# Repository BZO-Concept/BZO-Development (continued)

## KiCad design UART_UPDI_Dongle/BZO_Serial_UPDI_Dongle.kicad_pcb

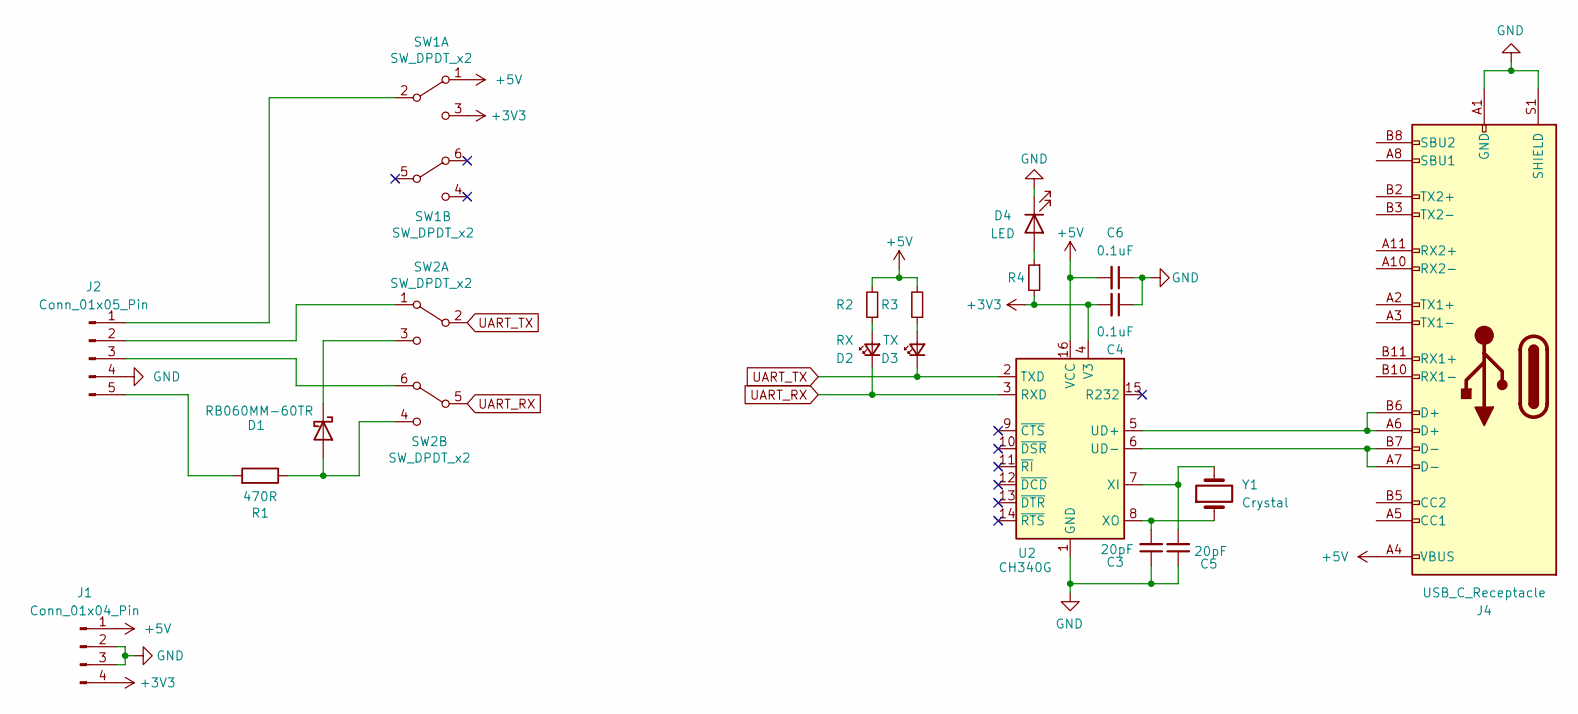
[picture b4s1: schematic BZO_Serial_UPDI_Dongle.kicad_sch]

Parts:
C3, C5: 20pF; C_0805_2012Metric_Pad1.18x1.45mm_HandSolder; LCSC Part # C0805C200J5HACTU
C4, C6: 0.1uF; C_0805_2012Metric_Pad1.18x1.45mm_HandSolder; LCSC Part # C0805C104J5RACTU
D1: RB060MM-60TR; LED_1206_3216Metric_Pad1.42x1.75mm_HandSolder(clean); Mouser Part Number 755-RB060MM-60TR
D2: RX; LED_1206_3216Metric_Pad1.42x1.75mm_HandSolder(clean); LCSC Part # //////////////////////////
D3: TX; LED_1206_3216Metric_Pad1.42x1.75mm_HandSolder(clean); LCSC Part # //////////////////////////
D4: LED; LED_1206_3216Metric_Pad1.42x1.75mm_HandSolder(clean); LCSC Part # //////////////////////////
J1: Conn_01x04_Pin; PinHeader_1x04_P2.54mm_Vertical; LCSC Part # //////////////////////////
J2: Conn_01x05_Pin; PinHeader_1x05_P2.54mm_Vertical; LCSC Part # //////////////////////////
J4: USB_C_Receptacle; USB_C_Receptacle_GCT_USB4085; LCSC Part # USB4085-GF-A
R1, R2, R3, R4: 470R; R_0805_2012Metric_Pad1.20x1.40mm_HandSolder; LCSC Part # CR0805-FX-4700ELF
SW1, SW2: SW_DPDT_x2; SMDIP-6_W7.62mm; LCSC Part # //////////////////////////
U2: CH340G; SOIC-16_3.9x9.9mm_P1.27mm; MANUFACTURER PART NUMBER CH340; LCSC Part # CH340G
Y1: Crystal; Crystal_SMD_HC49-SD

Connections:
+3V3: C4.2, J1.4, R4.2, SW1.3 (C), U2.4 (V3)
+5V: C6.2, J1.1, J4.A4 (VBUS), J4.A9 (VBUS), J4.B4 (VBUS), J4.B9 (VBUS), R2.2, R3.2, SW1.1 (A), U2.16 (VCC)
GND: C3.1, C4.1, C5.1, C6.1, D4.1 (K), J1.2, J1.3, J2.4, J4.A1 (GND), J4.A12 (GND), J4.B1 (GND), J4.B12 (GND), J4.S1 (SHIELD), U2.1 (GND)
unnamed: D1.2 (A), R1.1, SW2.4 (C)
unnamed: D1.1 (K), SW2.3 (C)
unnamed: D2.2 (A), R2.1
unnamed: D3.2 (A), R3.1
unnamed: D4.2 (A), R4.1
unnamed: J2.1, SW1.2 (B)
unnamed: J2.2, SW2.1 (A)
unnamed: J2.3, SW2.6 (A)
unnamed: J2.5, R1.2
unnamed: J4.A6 (D+), J4.B6 (D+), U2.5 (UD+)
unnamed: J4.A7 (D-), J4.B7 (D-), U2.6 (UD-)
unnamed: C5.2, U2.7 (XI), Y1.2
unnamed: C3.2, U2.8 (XO), Y1.1
UART_RX: D2.1 (K), SW2.5 (B), U2.3 (RXD)
UART_TX: D3.1 (K), SW2.2 (B), U2.2 (TXD)

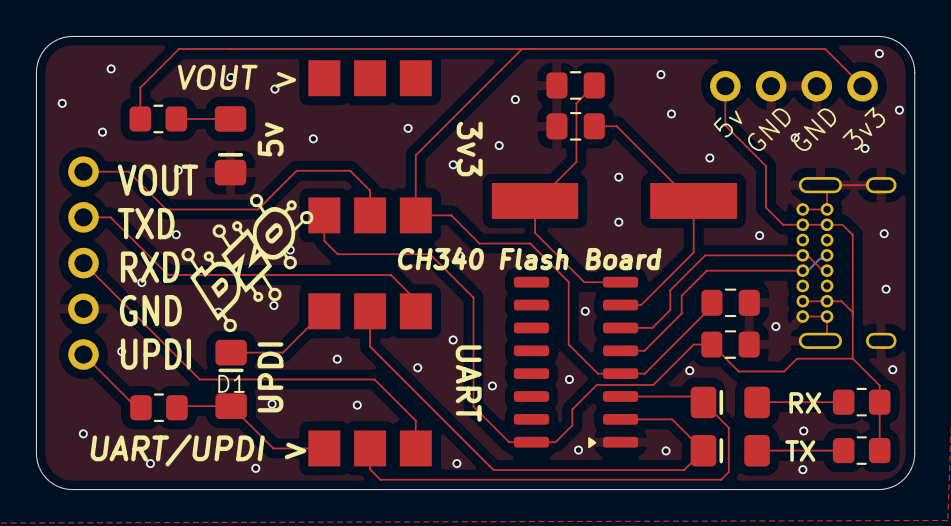
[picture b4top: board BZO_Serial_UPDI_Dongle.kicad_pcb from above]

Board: 2 copper layers, 48.8 x 25.2 mm, 19 parts (0 on the bottom side), 18 nets.

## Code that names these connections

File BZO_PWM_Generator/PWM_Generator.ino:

#include "BZO_PWM_Generator.h"

#define PinOUT1 PB0
#define PinOUT2 PB1
#define PinOUT3 PB10
#define PinOUT4 PB11

#define PinPOTvalue PA0
#define Frequence   150      //Hz
#define Duty        10       //%
#define WorkingValueMIN 50   //seuil min de traitement de la valeur
#define WorkingValueMAX 900  //seuil max de traitement de la valeur
#define DutyMIN   10         //valeur de Duty au seuil min %
#define DutyMAX   90         //valeur de Duty au seuil max %

uint16_t PotValue = 0;

void setup() {

  pinMode(PinPOTvalue, INPUT_ANALOG);
  //( Channel, Pin, Frequence, Duty, Valeur MIN, Valeur MAX, Duty/Freq MIN, Duty/Freq MAX)
  init_PWMG(1, PinOUT1, Frequence, 0, WorkingValueMIN, WorkingValueMAX, DutyMIN, DutyMAX);
  init_PWMG(2, PinOUT2, Frequence, 0, WorkingValueMIN, WorkingValueMAX, 90, 10);
  init_PWMG(3, PinOUT3, 0, Duty, WorkingValueMIN, WorkingValueMAX, 1, 100);
  init_PWMG(4, PinOUT4, 0, Duty, WorkingValueMIN, WorkingValueMAX, 100, 1);
}

void loop() {

//On calcule le Duty souhaité
  PotValue = analogRead(PinPOTvalue); 
  BZO_PWMG(1, PotValue);
  BZO_PWMG(2, PotValue);
  BZO_PWMG(3, PotValue);
  BZO_PWMG(4, PotValue);
}

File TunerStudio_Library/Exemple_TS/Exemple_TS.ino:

/********************************************************************************************
 *
 * Exemple d'utilisation de BZO_TS.h (base de communication TunerStudio)
 * A utiliser avec le fichier Exemple_TS.ini - mode d'emploi complet en tête de BZO_TS.h
 *
 * Mêmes noms que Speeduino : configPageX pour les réglages, currentStatus pour le temps réel.
 * (ici configPage1 = page 1 du .ini, configPage2 = page 2 : le numéro suit celui du .ini)
 *
 * Contact: www.bzo-concept.fr
 * v1.3 03/11/26
 *
 *******************************************************************************************/

#define TS_SIGNATURE      "BZO GPIO Base TS v1.0"   // = "signature" du .ini (TS : commence par "Speeduino")
//#define TS_PROTOCOLE_CRC                     // gros MCU (F103, F405...)
#define TS_EEPROM_VERSION 1                    // +1 à chaque changement de config1 / config2
#include "BZO_TS.h"            // 1. la lib
#include "globals.h"           // 2. réglages, currentStatus et liste du log TS : AVANT le reste

//************************************************************************************************************
// Boutons du .ini

bool SortieForcee = false;

void SortieON()  { SortieForcee = true;  }   // "E\x01\x01"
void SortieOFF() { SortieForcee = false; }   // "E\x01\x02"

//************************************************************************************************************

void setup()
{
  TS.addPage(1, configPage1);
  TS.addPage(2, configPage2);
  TS.setOutputs(getTSLogEntry, TS_LOG_TAILLE, currentStatus);   // temps réel façon Speeduino (liste dans globals.h)
  TS.addCommand(0x0101, SortieON);   // bouton "E\x01\x01" du .ini : on recopie les 2 octets après le E
  TS.addCommand(0x0102, SortieOFF);  // bouton "E\x01\x02"
  //Chaque fois que TS envoie la commande "E\x01\x01" (0x0101), la librairie appelle SortieON() une fois, pendant le TS.update()
  TS.begin(Serial, 115200);          // carte neuve : réglages à 0, charger la base tune (.msq) dans TS
  // ATTENTION STM32 : selon la carte choisie dans l'IDE, "Serial" n'est pas forcément l'UART câblée vers le PC
  // (F103 générique : Serial = USART2 sur PA3/PA2). Vérifier les broches, sinon déclarer l'UART à la main,
  // par exemple HardwareSerial SerialTS(PA10, PA9); puis TS.begin(SerialTS, 115200);
  // Tout ce qui lit les réglages (configPageX) au démarrage se fait APRÈS TS.begin() : c'est lui qui les relit en mémoire.
}

void loop()
{
  TS.update();

  bool sortieActive = configPage1.sortieActive || SortieForcee;

  // Valeurs simulées : à remplacer par les vraies mesures
  currentStatus.RPM             = (millis() / 10) % 7000;
  currentStatus.temperature     = 853 + configPage1.offsetTemperature;
  currentStatus.tension         = 1380;
  currentStatus.charge          = (millis() / 100) % 101;
  if (sortieActive == true) {currentStatus.rapportCyclique = configPage1.rapportCyclique;}
  else                      {currentStatus.rapportCyclique = 0;}
  currentStatus.sortieTable     = TS.table(configPage2.tableRegime, configPage2.tableCharge,
                                           configPage2.table, currentStatus.RPM, currentStatus.charge);
  currentStatus.sortieOn        = sortieActive;
  currentStatus.alarme          = (currentStatus.tension < configPage1.tensionMin);
}
